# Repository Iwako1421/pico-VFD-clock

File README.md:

# pico-VFD-clock
simple VFD clock using raspberry pi pico

## 部品表
|基板上の表記|値・部品番号|秋月電子通販コード(旧)|
|:----|:----|:----|
|C1|4.7u|P-08154|
|C2|0.33u|P-08147|
|C3|0.33u|P-08147|
|C4|4.7u|P-08154|
|C5|4.7u|P-08154|
|C6|4.7u|P-08154|
|C7|0.1u|P-15927|
|C8|0.1u|P-15927|
|C9|0.1u|P-15927|
|SW1|SET|P-03647|
|SW2|ADJ|P-03647|
|U1|MAX662|I-01165|
|U2|Raspberry Pi Pico|M-16132|
|U3|UT7500L-25-T92-B-K|I-10268|
|U4|TBD62783A|I-10957|
|U5|TBD62783A|I-10957|
|U6|TBD62783A|I-10957|
|U7|LD8195|付属(名古屋大須・ボントンで入手)|

## 組み立て方
1. 部品表を見ながら部品をはんだ付けします
2. このgithubリポジトリ (https://github.com/Iwako1421/pico-VFD-clock) をzipでダウンロードし、解凍してprogram/VFDclock.uf2を取り出します
3. raspberry pi picoのbootselボタンを押しながらmicroUSBケーブルでPCと接続します
4. raspberry pi picoがストレージとして認識されるので、そこにVFDclock.uf2をドラッグ&ドロップします
5. 時刻を合わせて完成

## 時刻合わせ方法
ADJキーを押すたびに通常表示→時間合わせ→分合わせ→秒合わせ→12時制/24時制切り替え→通常表示と切り替わります。合わせたい項目のモードにADJキーで切り替えて、SETキーを押して調整した後ADJキーで通常表示に戻ってください。

## 電源について
USB-MicroBケーブルで給電してください。コネクタが外れやすいので、ケーブルを抜くときは大きくこじらずにまっすぐ引き抜いてください。

## 注意
VFDはガラス製です。割れやすい (特に突起部分) ので、落としたりぶつけたりしないよう十分ご注意ください。

## 質問等
制作者Twitter (@iwamechatronics) またはEmail (k_iwakura1421@outlook.jp) までご連絡ください。

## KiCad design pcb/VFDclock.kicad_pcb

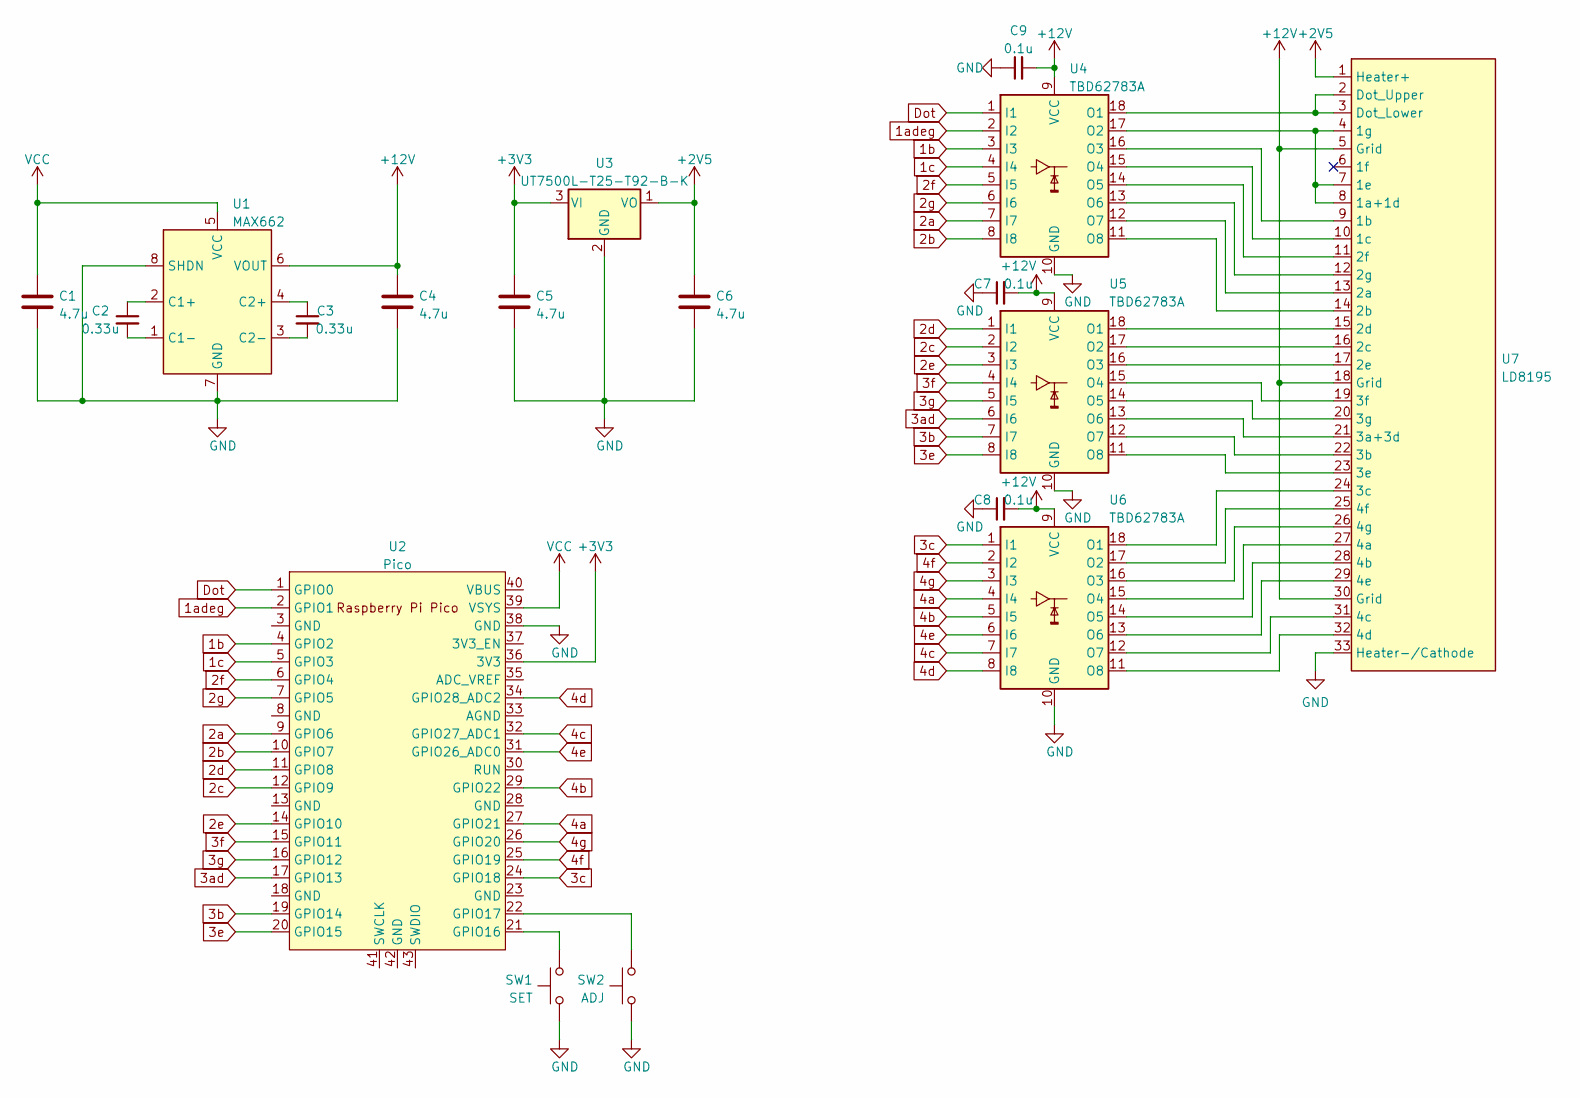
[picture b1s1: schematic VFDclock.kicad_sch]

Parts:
C1, C4, C5, C6: 4.7u; C_Disc_D5.1mm_W3.2mm_P5.00mm
C2, C3: 0.33u; C_Disc_D5.0mm_W2.5mm_P5.00mm
C7, C8, C9: 0.1u; C_Disc_D5.0mm_W2.5mm_P5.00mm
SW1: SET; SW_PUSH_6mm_H7.3mm
SW2: ADJ; SW_PUSH_6mm_H7.3mm
U1: MAX662; DIP-8_W7.62mm_Socket
U2: Pico; RPi_Pico_SMD_TH
U3: UT7500L-T25-T92-B-K; TO-92_Inline_Wide
U4, U5, U6: TBD62783A; DIP-18_W7.62mm_Socket
U7: LD8195; PinSocket_1x33_P2.54mm_Vertical

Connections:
1adeg: U2.2 (GPIO1), U4.2 (I2)
1b: U2.4 (GPIO2), U4.3 (I3)
1c: U2.5 (GPIO3), U4.4 (I4)
2a: U2.9 (GPIO6), U4.7 (I7)
2b: U2.10 (GPIO7), U4.8 (I8)
2c: U2.12 (GPIO9), U5.2 (I2)
2d: U2.11 (GPIO8), U5.1 (I1)
2e: U2.14 (GPIO10), U5.3 (I3)
2f: U2.6 (GPIO4), U4.5 (I5)
2g: U2.7 (GPIO5), U4.6 (I6)
3ad: U2.17 (GPIO13), U5.6 (I6)
3b: U2.19 (GPIO14), U5.7 (I7)
3c: U2.24 (GPIO18), U6.1 (I1)
3e: U2.20 (GPIO15), U5.8 (I8)
3f: U2.15 (GPIO11), U5.4 (I4)
3g: U2.16 (GPIO12), U5.5 (I5)
4a: U2.27 (GPIO21), U6.4 (I4)
4b: U2.29 (GPIO22), U6.5 (I5)
4c: U2.32 (GPIO27_ADC1), U6.7 (I7)
4d: U2.34 (GPIO28_ADC2), U6.8 (I8)
4e: U2.31 (GPIO26_ADC0), U6.6 (I6)
4f: U2.25 (GPIO19), U6.2 (I2)
4g: U2.26 (GPIO20), U6.3 (I3)
+2V5: C6.1, U3.1 (VO), U7.1 (Heater+)
+3V3: C5.1, U2.36 (3V3), U3.3 (VI)
+12V: C4.1, C7.2, C8.2, C9.2, U1.6 (VOUT), U4.9 (VCC), U5.9 (VCC), U6.9 (VCC), U7.5 (Grid), U7.18 (Grid), U7.30 (Grid)
Dot: U2.1 (GPIO0), U4.1 (I1)
GND: C1.2, C4.2, C5.2, C6.2, C7.1, C8.1, C9.1, SW1.2, SW2.2, U1.7 (GND), U1.8 (SHDN), U2.38 (GND), U3.2 (GND), U4.10 (GND), U5.10 (GND), U6.10 (GND), U7.33 (Heater-/Cathode)
unnamed: C2.1, U1.2 (C1+)
unnamed: C2.2, U1.1 (C1-)
unnamed: C3.1, U1.4 (C2+)
unnamed: C3.2, U1.3 (C2-)
unnamed: U4.11 (O8), U7.14 (2b)
unnamed: U4.12 (O7), U7.13 (2a)
unnamed: U4.13 (O6), U7.12 (2g)
unnamed: U4.14 (O5), U7.11 (2f)
unnamed: U4.15 (O4), U7.10 (1c)
unnamed: U4.16 (O3), U7.9 (1b)
unnamed: U4.17 (O2), U7.4 (1g), U7.7 (1e), U7.8 (1a+1d)
unnamed: U4.18 (O1), U7.2 (Dot_Upper), U7.3 (Dot_Lower)
unnamed: U5.11 (O8), U7.23 (3e)
unnamed: U5.12 (O7), U7.22 (3b)
unnamed: U5.13 (O6), U7.21 (3a+3d)
unnamed: U5.14 (O5), U7.20 (3g)
unnamed: U5.15 (O4), U7.19 (3f)
unnamed: U5.16 (O3), U7.17 (2e)
unnamed: U5.17 (O2), U7.16 (2c)
unnamed: U5.18 (O1), U7.15 (2d)
unnamed: U6.11 (O8), U7.32 (4d)
unnamed: U6.12 (O7), U7.31 (4c)
unnamed: U6.13 (O6), U7.29 (4e)
unnamed: U6.14 (O5), U7.28 (4b)
unnamed: U6.15 (O4), U7.27 (4a)
unnamed: U6.16 (O3), U7.26 (4g)
unnamed: U6.17 (O2), U7.25 (4f)
unnamed: U6.18 (O1), U7.24 (3c)
VCC: C1.1, U1.5 (VCC), U2.39 (VSYS)

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
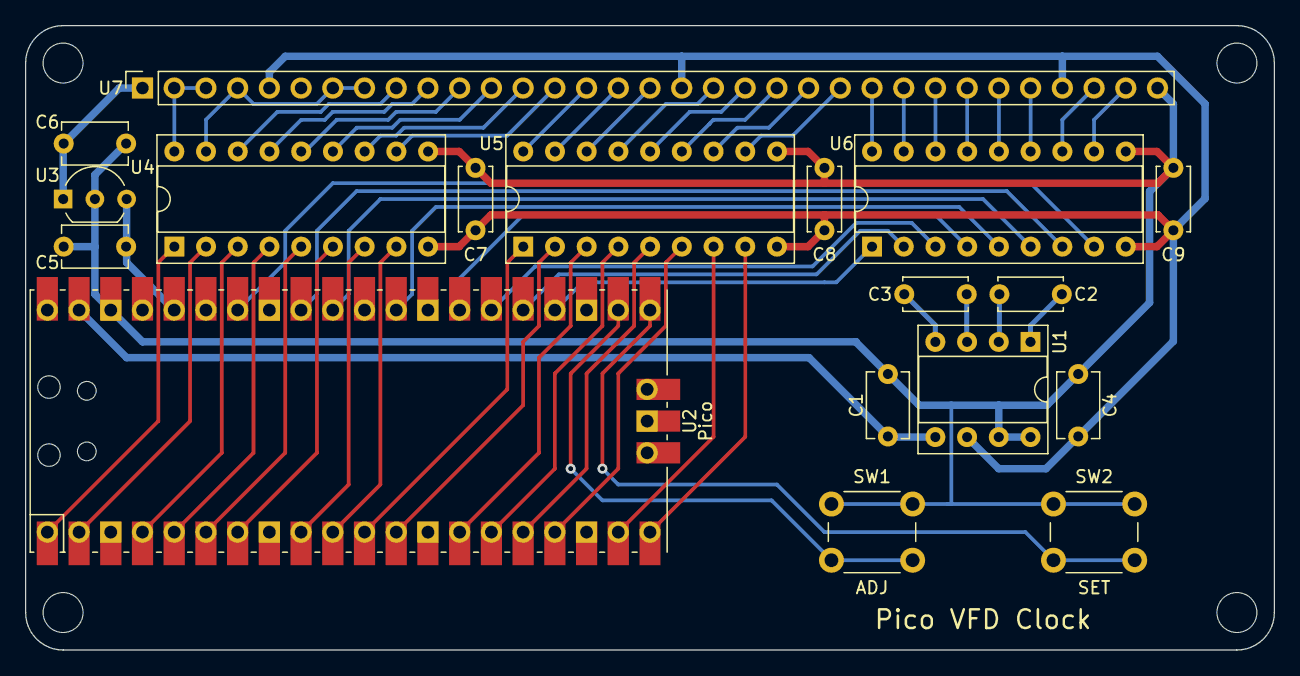
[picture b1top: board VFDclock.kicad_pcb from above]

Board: 2 copper layers, 100.0 x 50.0 mm, 18 parts (0 on the bottom side), 59 nets.

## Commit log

2024-03-21 add files
